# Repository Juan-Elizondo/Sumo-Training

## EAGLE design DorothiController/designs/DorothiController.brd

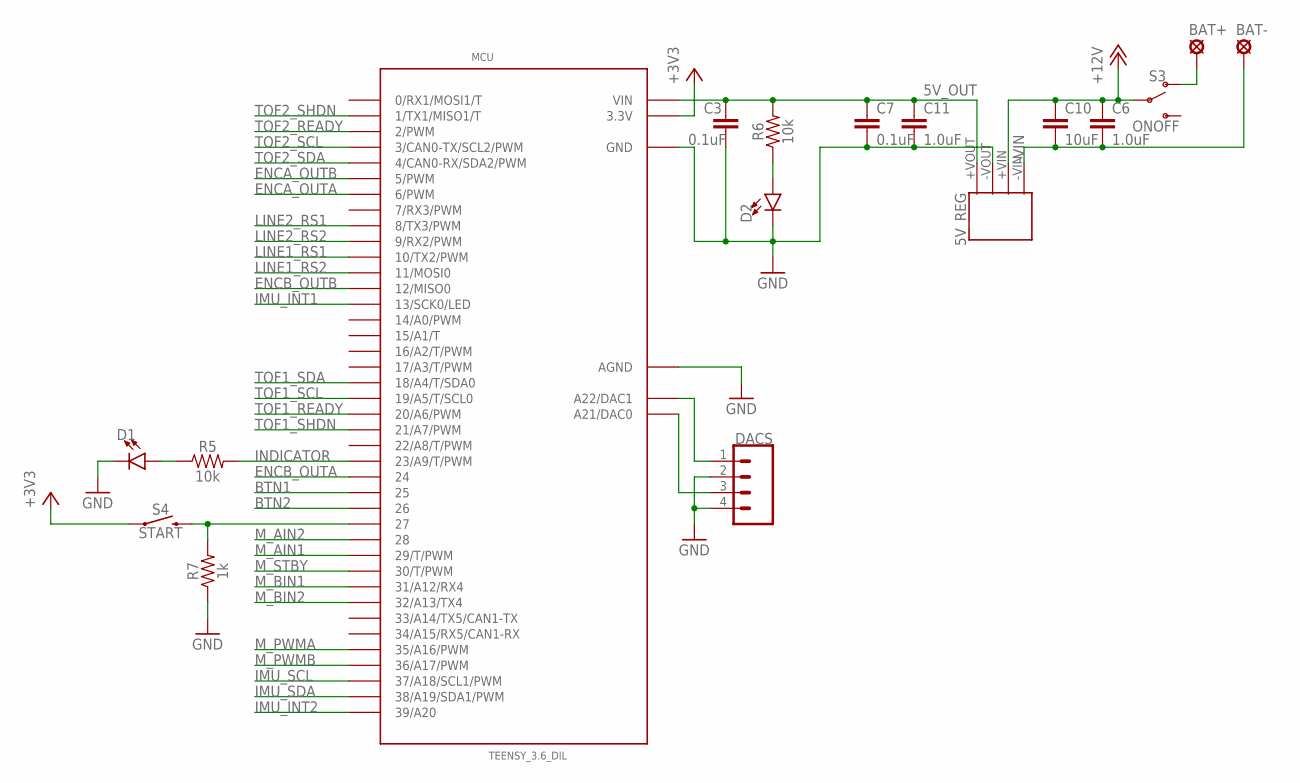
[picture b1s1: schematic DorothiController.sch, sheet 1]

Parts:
5V_REG: CRE1S1205SC
BAT+: 24_SOLPAD; WIRE_SOLPAD
BAT-: 24_SOLPAD; WIRE_SOLPAD
C3, C7: 0.1uF; 0603
C6, C11: 1.0uF; 0603
C10: 10uF; 0603
D1, D2: LED0603; LED-0603
DACS: CONN_04; 1X04
MCU: TEENSY_3.6_DIL
R5, R6: 10k; 0603
R7: 1k; 0603
S3: ONOFF; SWITCH_SPDT_PTH_11.6X4.0MM
S4: START; TACTILE_SWITCH_SMD_6.0X3.5MM

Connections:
5V_OUT: 5V_REG.+VOUT, C3.1, C7.1, C11.1, MCU.VIN, R6.2
+3V3: MCU.3.3V, MCU.3.3V3 (3.3V), S4.1; also elsewhere on the board
+12V: 5V_REG.+VIN, C6.1, C10.1, S3.2; also elsewhere on the board
+VIN: BAT+.P$1, S3.1 (O)
-VIN: 5V_REG.-VIN, BAT-.P$1, C6.2, C10.2
BTN1: MCU.25; also elsewhere on the board
BTN2: MCU.26; also elsewhere on the board
DAC1: DACS.1, MCU.A22 (A22/DAC1)
DAC2: DACS.3, MCU.A21 (A21/DAC0)
ENCA_OUTA: MCU.6 (6/PWM); also elsewhere on the board
ENCA_OUTB: MCU.5 (5/PWM); also elsewhere on the board
ENCB_OUTA: MCU.24; also elsewhere on the board
ENCB_OUTB: MCU.12 (12/MISO0); also elsewhere on the board
GND: 5V_REG.-VOUT, C3.2, C7.2, C11.2, D1.C, D2.C, DACS.2, DACS.4, MCU.AGND, MCU.GND, MCU.GND1 (GND), R7.1; also elsewhere on the board
IMU_INT1: MCU.13 (13/SCK0/LED); also elsewhere on the board
IMU_INT2: MCU.39/A20; also elsewhere on the board
IMU_SCL: MCU.37/A18 (37/A18/SCL1/PWM); also elsewhere on the board
IMU_SDA: MCU.38/A19 (38/A19/SDA1/PWM); also elsewhere on the board
INDICATOR: MCU.23/A9 (23/A9/T/PWM), R5.2
LINE1_RS1: MCU.10 (10/TX2/PWM); also elsewhere on the board
LINE1_RS2: MCU.11 (11/MOSI0); also elsewhere on the board
LINE2_RS1: MCU.8 (8/TX3/PWM); also elsewhere on the board
LINE2_RS2: MCU.9 (9/RX2/PWM); also elsewhere on the board
M_AIN1: MCU.29 (29/T/PWM); also elsewhere on the board
M_AIN2: MCU.28; also elsewhere on the board
M_BIN1: MCU.31/A12 (31/A12/RX4); also elsewhere on the board
M_BIN2: MCU.32/A13 (32/A13/TX4); also elsewhere on the board
M_PWMA: MCU.35/A16 (35/A16/PWM); also elsewhere on the board
M_PWMB: MCU.36/A17 (36/A17/PWM); also elsewhere on the board
M_STBY: MCU.30 (30/T/PWM); also elsewhere on the board
unnamed: D1.A, R5.1
unnamed: D2.A, R6.1
START: MCU.27, R7.2, S4.2
TOF1_READY: MCU.20/A6 (20/A6/PWM); also elsewhere on the board
TOF1_SCL: MCU.19/A5 (19/A5/T/SCL0); also elsewhere on the board
TOF1_SDA: MCU.18/A4 (18/A4/T/SDA0); also elsewhere on the board
TOF1_SHDN: MCU.21/A7 (21/A7/PWM); also elsewhere on the board
TOF2_READY: MCU.2 (2/PWM); also elsewhere on the board
TOF2_SCL: MCU.3 (3/CAN0-TX/SCL2/PWM); also elsewhere on the board
TOF2_SDA: MCU.4 (4/CAN0-RX/SDA2/PWM); also elsewhere on the board
TOF2_SHDN: MCU.1 (1/TX1/MISO1/T); also elsewhere on the board

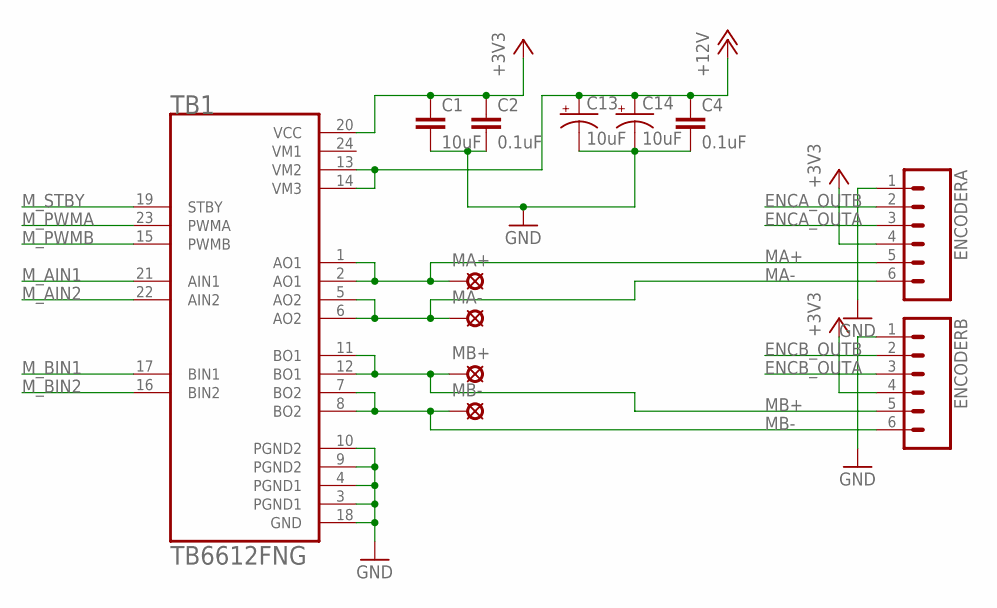
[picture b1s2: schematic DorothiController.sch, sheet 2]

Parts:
C1: 10uF; 0603
C2, C4: 0.1uF; 0603
C13, C14: 10uF; 0603-POLAR
ENCODERA: CONN_06SILK_FEMALE_PTH; 1X06
ENCODERB: CONN_06SILK_FEMALE_PTH; 1X06
MA+: 24_SOLPAD; WIRE_SOLPAD
MA-: 24_SOLPAD; WIRE_SOLPAD
MB+: 24_SOLPAD; WIRE_SOLPAD
MB-: 24_SOLPAD; WIRE_SOLPAD
TB1: TB6612FNG; SOP65P760X160-24N

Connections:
+3V3: C1.1, C2.1, ENCODERA.4, ENCODERB.4, TB1.20 (VCC); also elsewhere on the board
+12V: C4.1, C13.+, C14.+, TB1.13 (VM2), TB1.14 (VM3); also elsewhere on the board
ENCA_OUTA: ENCODERA.3; also elsewhere on the board
ENCA_OUTB: ENCODERA.2; also elsewhere on the board
ENCB_OUTA: ENCODERB.3; also elsewhere on the board
ENCB_OUTB: ENCODERB.2; also elsewhere on the board
GND: C1.2, C2.2, C4.2, C13.-, C14.-, ENCODERA.1, ENCODERB.1, TB1.3 (PGND1), TB1.4 (PGND1), TB1.9 (PGND2), TB1.10 (PGND2), TB1.18 (GND); also elsewhere on the board
MA+: ENCODERA.5, MA+.P$1, TB1.1 (AO1), TB1.2 (AO1)
MA-: ENCODERA.6, MA-.P$1, TB1.5 (AO2), TB1.6 (AO2)
MB+: ENCODERB.5, MB+.P$1, TB1.11 (BO1), TB1.12 (BO1)
MB-: ENCODERB.6, MB-.P$1, TB1.7 (BO2), TB1.8 (BO2)
M_AIN1: TB1.21 (AIN1); also elsewhere on the board
M_AIN2: TB1.22 (AIN2); also elsewhere on the board
M_BIN1: TB1.17 (BIN1); also elsewhere on the board
M_BIN2: TB1.16 (BIN2); also elsewhere on the board
M_PWMA: TB1.23 (PWMA); also elsewhere on the board
M_PWMB: TB1.15 (PWMB); also elsewhere on the board
M_STBY: TB1.19 (STBY); also elsewhere on the board
VM1: TB1.24 (VM1)

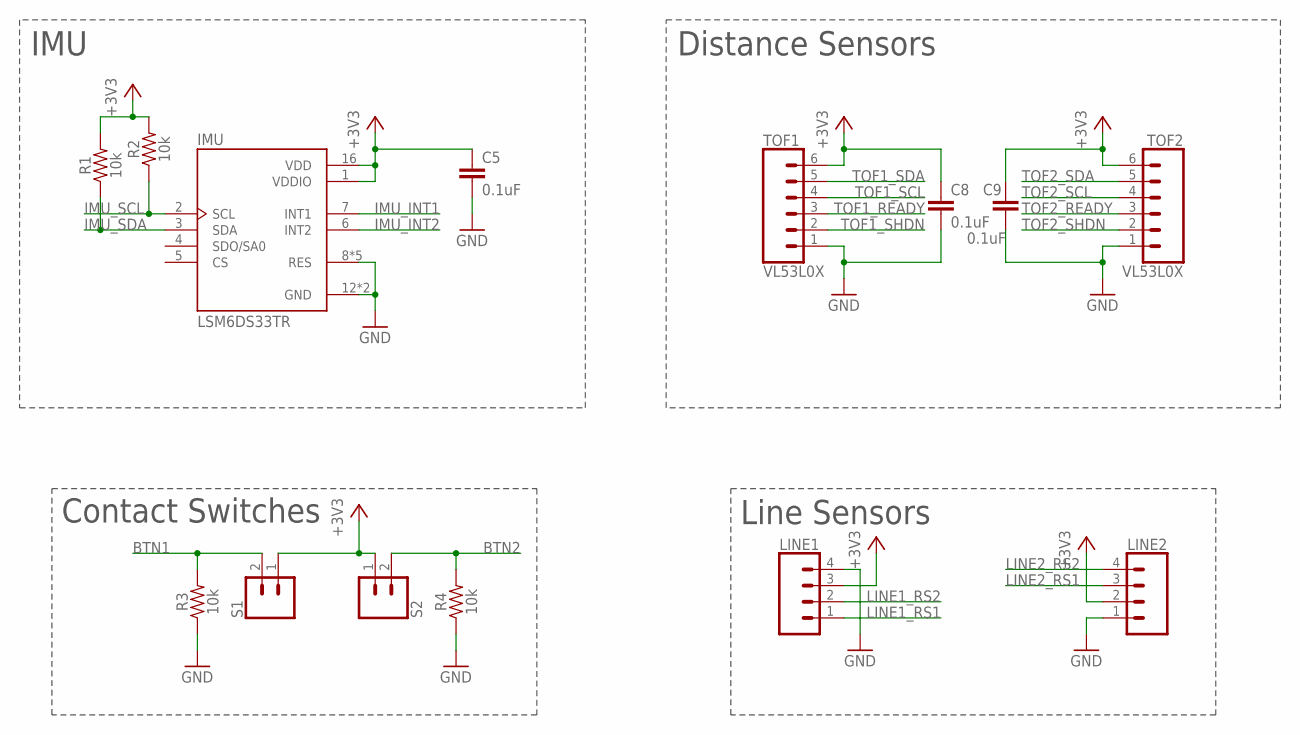
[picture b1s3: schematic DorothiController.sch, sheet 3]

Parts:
C5, C8, C9: 0.1uF; 0603
IMU: LSM6DS33TR; PQFN50P300X300X86-16N
LINE1, LINE2: CONN_04; 1X04
R1, R2, R3, R4: 10k; 0603
S1, S2: CONN_02; 1X02
TOF1, TOF2: VL53L0X; 1X06

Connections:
+3V3: C5.1, C8.1, C9.1, IMU.1 (VDDIO), IMU.16 (VDD), LINE1.3, LINE2.2, R1.2, R2.2, S1.1, S2.1, TOF1.6, TOF2.6; also elsewhere on the board
BTN1: R3.2, S1.2; also elsewhere on the board
BTN2: R4.2, S2.2; also elsewhere on the board
GND: C5.2, C8.2, C9.2, IMU.8 (RES), IMU.9 (RES), IMU.10 (RES), IMU.11 (RES), IMU.12 (GND), IMU.13 (GND), IMU.15 (RES), LINE1.4, LINE2.1, R3.1, R4.1, TOF1.1, TOF2.1; also elsewhere on the board
IMU_INT1: IMU.7 (INT1); also elsewhere on the board
IMU_INT2: IMU.6 (INT2); also elsewhere on the board
IMU_SCL: IMU.2 (SCL), R2.1; also elsewhere on the board
IMU_SDA: IMU.3 (SDA), R1.1; also elsewhere on the board
LINE1_RS1: LINE1.1; also elsewhere on the board
LINE1_RS2: LINE1.2; also elsewhere on the board
LINE2_RS1: LINE2.3; also elsewhere on the board
LINE2_RS2: LINE2.4; also elsewhere on the board
TOF1_READY: TOF1.3; also elsewhere on the board
TOF1_SCL: TOF1.4; also elsewhere on the board
TOF1_SDA: TOF1.5; also elsewhere on the board
TOF1_SHDN: TOF1.2; also elsewhere on the board
TOF2_READY: TOF2.3; also elsewhere on the board
TOF2_SCL: TOF2.4; also elsewhere on the board
TOF2_SDA: TOF2.5; also elsewhere on the board
TOF2_SHDN: TOF2.2; also elsewhere on the board

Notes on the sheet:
IMU
Distance Sensors
Line Sensors
Contact Switches

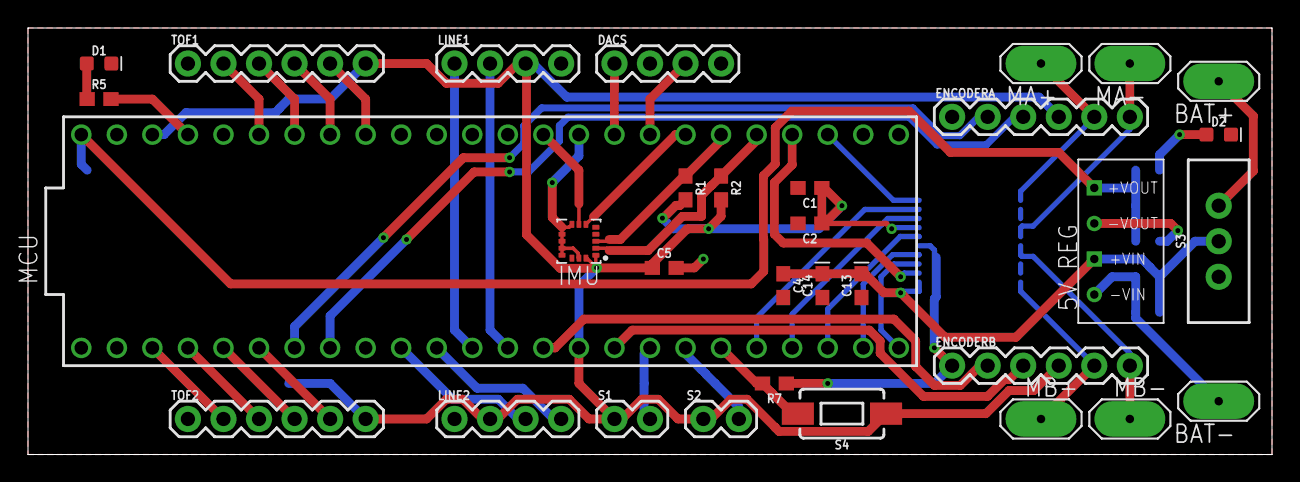
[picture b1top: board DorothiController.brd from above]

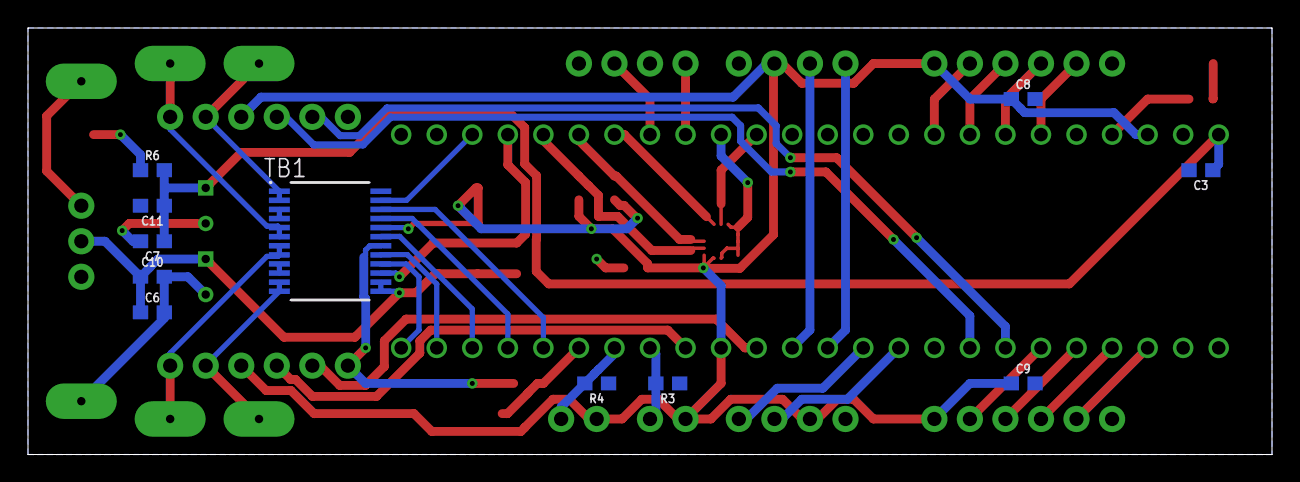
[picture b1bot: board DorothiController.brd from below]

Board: 2 copper layers, 88.9 x 30.5 mm, 43 parts (11 on the bottom side), 45 nets.

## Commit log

2018-03-31 Create DistSensor_2
2018-03-31 Rename DistSensor_2 to DistSensor_2.ino
2018-03-31 Rename Senors/DistSensor_2.ino to Sensors/DualDistSensor.ino
2018-04-02 Create RetreatFromWall
2018-04-07 Create AllSensorsAndDrive
2018-10-09 added e-training week 1 stuff
2018-11-29 dorothicontroller
2018-11-30 tof sensor
2018-11-30 silk screen and status diode added
2018-12-01 forgot resistor
2019-01-27 new 2 layer board with encoders

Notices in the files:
parts and their libraries:
SparkFun-Connectors: Licensing: Creative Commons ShareAlike 4.0 International - https://creativecommons.org/licenses/by-sa/4.0
